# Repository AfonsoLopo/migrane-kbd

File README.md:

## MIGRANE

# Table of Contents: 
- [Specs](#Specs)
- [Assembly](#Assemby)
- [Firmware](#Firmware)

## Specs
<b>MCU</b> : STM32F446RCT6
<b>Number of Keys:</b> 64 Kailh choc hotswap sockets
<b>Number of LEDS:</b> 64 SK6812-mini e (1 per key) 
<b>Displays:</b> Adafruit 1.8" TFT Display
<b>Connection between halfs :</b> Serial over USB-C to USB-C cable
<b>Wire Debugger:</b> optional headers

## Assembly

    (TBD)

## Firmware

Board prepared to be used with qmk firmware.

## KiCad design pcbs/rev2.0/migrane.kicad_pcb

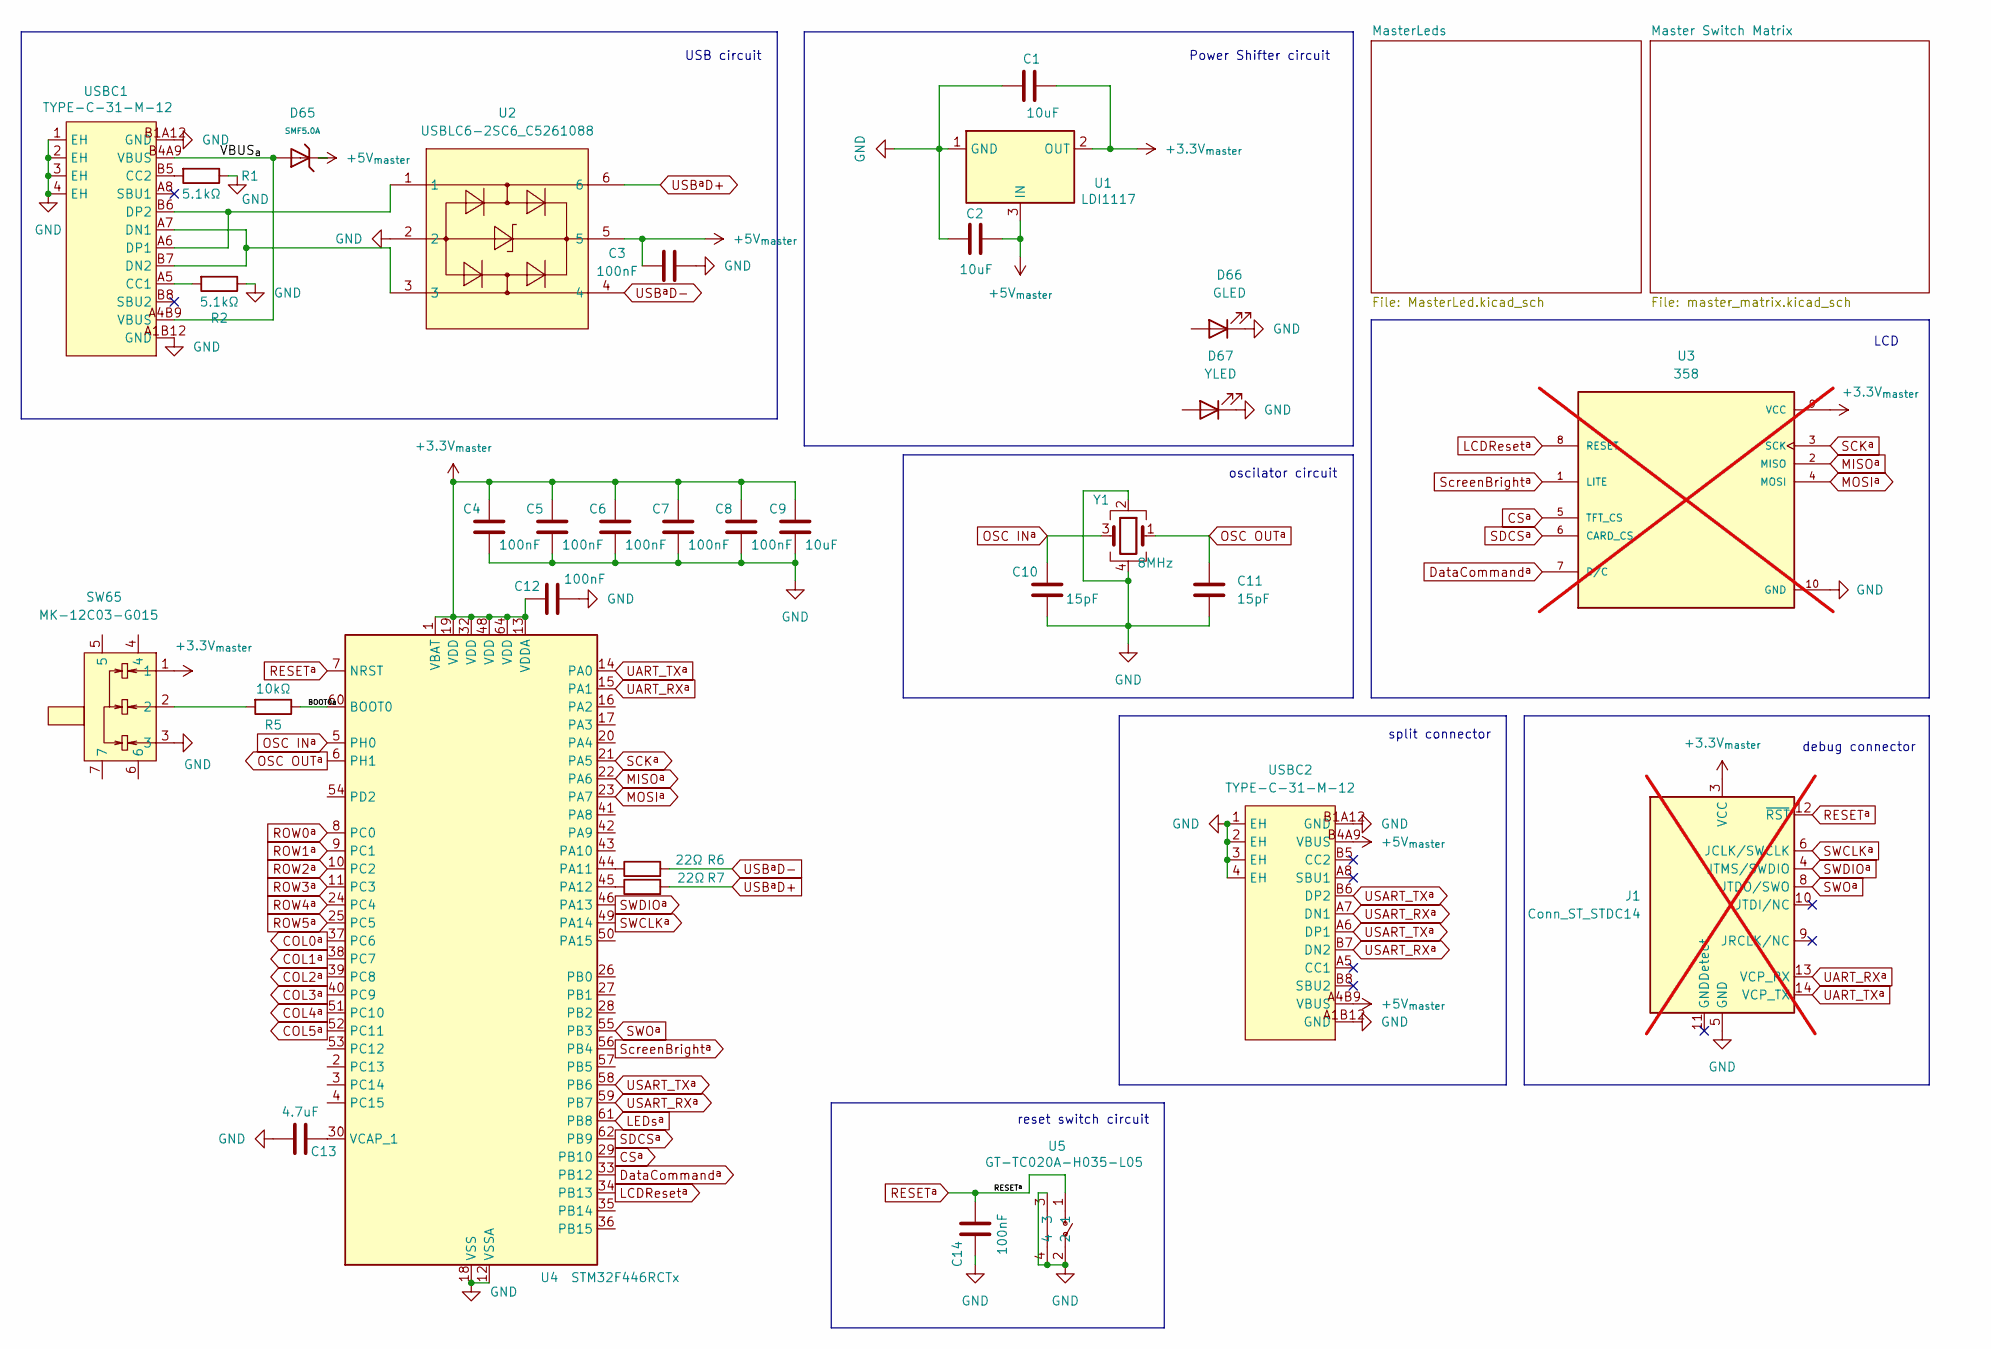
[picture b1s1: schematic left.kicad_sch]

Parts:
C1, C2, C9: 10uF; C_1206_3216Metric; LCSC C13585
C3, C4, C5, C6, C7, C8, C12, C14: 100nF; C_0805_2012Metric; LCSC C48579599
C10, C11: 15pF; C_0402_1005Metric; LCSC C441742
C13: 4.7uF; C_0603_1608Metric; LCSC C1705
D65: SMF5.0A; D_SOD-123FL; Part SMF5.0A; LCSC C19077497
D66: GLED; LED0805-R-RD; LCSC C84260
D67: YLED; LED0805-R-RD; LCSC C84261
J1: Conn_ST_STDC14; PinHeader_2x07_P1.27mm_Horizontal; not fitted
R1, R2: 5.1kΩ; R_0603_1608Metric; LCSC C2907114
R5: 10kΩ; R_0805_2012Metric; LCSC C84376
R6, R7: 22Ω; R_0402_1005Metric; LCSC C2906914
SW65: MK-12C03-G015; SW-SMD_MK-12C03-G015; LCSC Part C2890358
U1: LDI1117; SOT-223-3_TabPin2; LCSC C6186
U2: USBLC6-2SC6_C5261088; SOT-23-6_L2.9-W1.6-P0.95-LS2.8-BR; LCSC Part C5261088
U3: 358; MODULE_358; PARTREV 2021-12-09; not fitted
U4: STM32F446RCTx; LQFP-64_10x10mm_P0.5mm; LCSC C915971
U5: GT-TC020A-H035-L05; SW-SMD_GT-TC020B-H035-L05; LCSC Part C17179533
USBC1, USBC2: TYPE-C-31-M-12; USB-C_SMD-TYPE-C-31-M-12_1; LCSC Part C165948
Y1: 8MHz; Crystal_SMD_Abracon_ABM3B-4Pin_5.0x3.2mm; LCSC C1985378

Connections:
+3.3V_{master}: C1.1, C4.1, C5.1, C6.1, C7.1, C8.1, C9.1, C12.1, J1.3 (VCC), SW65.1, U1.2 (OUT), U3.9 (VCC), U4.1 (VBAT), U4.13 (VDDA), U4.19 (VDD), U4.32 (VDD), U4.48 (VDD), U4.64 (VDD); also elsewhere on the board
+5V_{master}: C2.2, C3.1, D65.1, U1.3 (IN), U2.5, USBC2.A4B9 (VBUS), USBC2.B4A9 (VBUS); also elsewhere on the board
/left/BOOT0a: R5.1, U4.60 (BOOT0)
/left/VBUS_{a}: D65.2, USBC1.A4B9 (VBUS), USBC1.B4A9 (VBUS)
COL0^{a}: U4.37 (PC6); also elsewhere on the board
COL1^{a}: U4.38 (PC7); also elsewhere on the board
COL2^{a}: U4.39 (PC8); also elsewhere on the board
COL3^{a}: U4.40 (PC9); also elsewhere on the board
COL4^{a}: U4.51 (PC10); also elsewhere on the board
COL5^{a}: U4.52 (PC11); also elsewhere on the board
CS^{a}: U3.5 (TFT_CS), U4.29 (PB10); also elsewhere on the board
DataCommand^{a}: U3.7 (D/C), U4.33 (PB12); also elsewhere on the board
GND: C1.2, C2.1, C3.2, C4.2, C5.2, C6.2, C7.2, C8.2, C9.2, C10.2, C11.2, C12.2, C13.1, C14.1, D66.1 (K), D67.1 (K), J1.5 (GND), J1.7 (GND), R1.1, R2.1, SW65.3, U1.1 (GND), U2.2, U3.10 (GND), U4.12 (VSSA), U4.18 (VSS), U4.31 (VSS), U4.47 (VSS), U4.63 (VSS), U5.2, U5.3, U5.4, USBC1.1 (EH), USBC1.2 (EH), USBC1.3 (EH), USBC1.4 (EH), USBC1.A1B12 (GND), USBC1.B1A12 (GND), USBC2.1 (EH), USBC2.2 (EH), USBC2.3 (EH), USBC2.4 (EH), USBC2.A1B12 (GND), USBC2.B1A12 (GND), Y1.2, Y1.4; also elsewhere on the board
LCDReset^{a}: U3.8 (RESET), U4.34 (PB13); also elsewhere on the board
LEDs^{a}: U4.61 (PB8); also elsewhere on the board
MISO^{a}: U3.2 (MISO), U4.22 (PA6); also elsewhere on the board
MOSI^{a}: U3.4 (MOSI), U4.23 (PA7); also elsewhere on the board
unnamed: R5.2, SW65.2
unnamed 175: R6.1, U4.44 (PA11); also elsewhere on the board
unnamed 176: R7.1, U4.45 (PA12); also elsewhere on the board
unnamed: C13.2, U4.30 (VCAP_1)
unnamed: R2.2, USBC1.A5 (CC1)
unnamed: R1.2, USBC1.B5 (CC2)
unnamed: U2.3, USBC1.A7 (DN1), USBC1.B7 (DN2)
unnamed: U2.1, USBC1.A6 (DP1), USBC1.B6 (DP2)
OSC IN^{a}: C10.1, U4.5 (PH0), Y1.3
OSC OUT^{a}: C11.1, U4.6 (PH1), Y1.1
RESET^{a}: C14.2, J1.12 (~RST), U4.7 (NRST), U5.1; also elsewhere on the board
ROW0^{a}: U4.8 (PC0); also elsewhere on the board
ROW1^{a}: U4.9 (PC1); also elsewhere on the board
ROW2^{a}: U4.10 (PC2); also elsewhere on the board
ROW3^{a}: U4.11 (PC3); also elsewhere on the board
ROW4^{a}: U4.24 (PC4); also elsewhere on the board
ROW5^{a}: U4.25 (PC5); also elsewhere on the board
SCK^{a}: U3.3 (SCK), U4.21 (PA5); also elsewhere on the board
SDCS^{a}: U3.6 (CARD_CS), U4.62 (PB9); also elsewhere on the board
SWCLK^{a}: J1.6 (JCLK/SWCLK), U4.49 (PA14); also elsewhere on the board
SWDIO^{a}: J1.4 (JTMS/SWDIO), U4.46 (PA13); also elsewhere on the board
SWO^{a}: J1.8 (JTDO/SWO), U4.55 (PB3); also elsewhere on the board
ScreenBright^{a}: U3.1 (LITE), U4.56 (PB4); also elsewhere on the board
UART_RX^{a}: J1.13 (VCP_RX), U4.15 (PA1); also elsewhere on the board
UART_TX^{a}: J1.14 (VCP_TX), U4.14 (PA0); also elsewhere on the board
USART_RX^{a}: U4.59 (PB7), USBC2.A7 (DN1), USBC2.B7 (DN2)
USART_TX^{a}: U4.58 (PB6), USBC2.A6 (DP1), USBC2.B6 (DP2)
USB^{a}D+: R7.2, U2.6
USB^{a}D-: R6.2, U2.4

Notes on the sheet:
split connector
oscilator circuit
reset switch circuit
debug connector
USB circuit
Power Shifter circuit
LCD

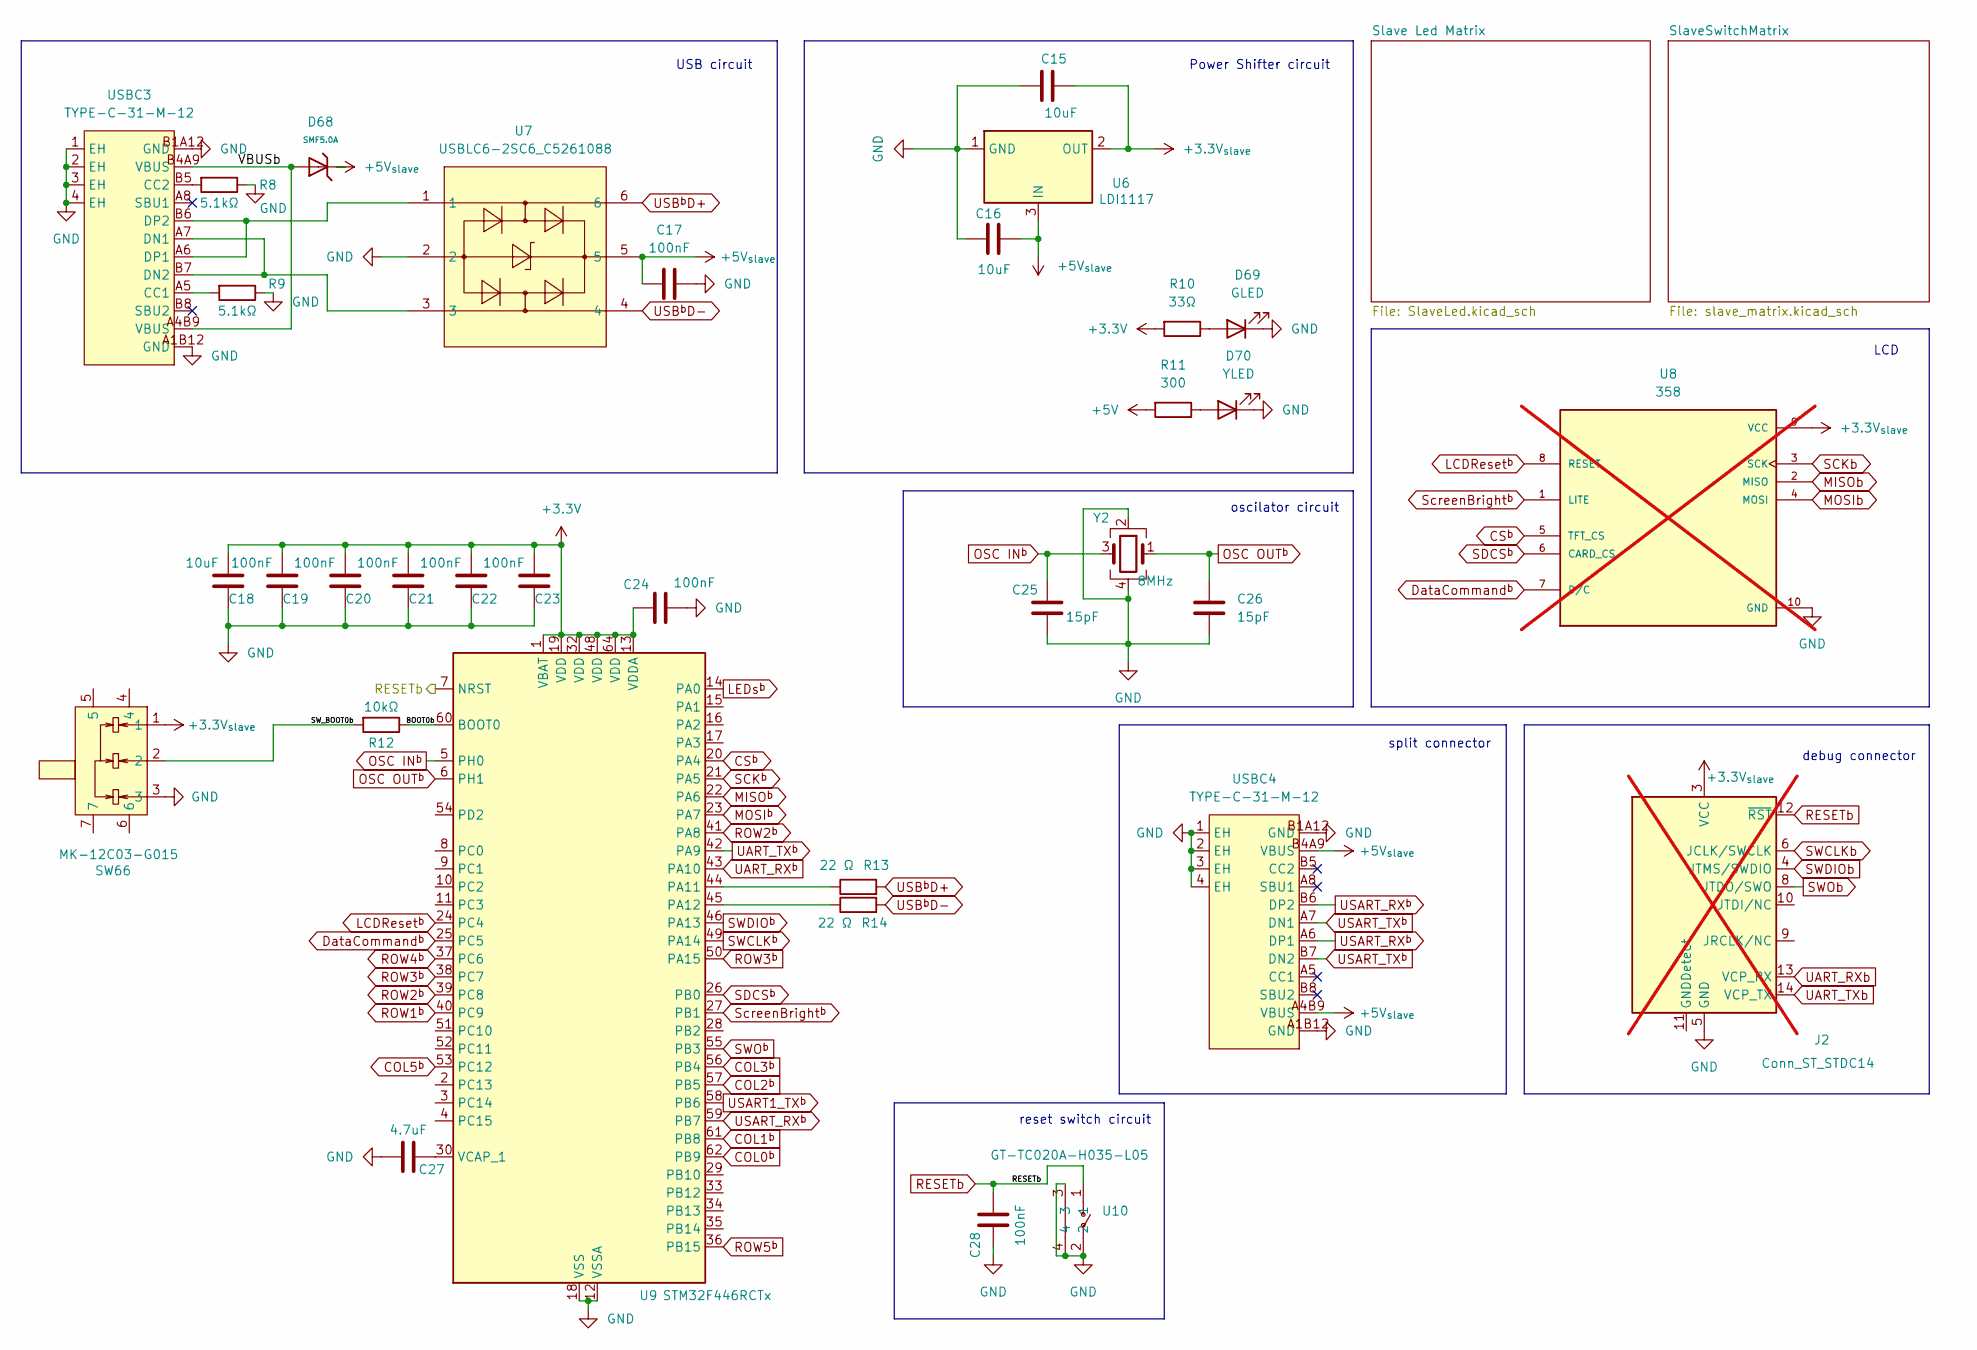
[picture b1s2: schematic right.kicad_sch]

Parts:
C15, C16, C18: 10uF; C_1206_3216Metric; LCSC C13585
C17, C19, C20, C21, C22, C23, C24, C28: 100nF; C_0805_2012Metric; LCSC C48579599
C25, C26: 15pF; C_0402_1005Metric; LCSC C441742
C27: 4.7uF; C_0603_1608Metric; LCSC C1705
D68: SMF5.0A; D_SOD-123FL; Part SMF5.0A; LCSC C19077497
D69: GLED; LED0805-R-RD; LCSC C84260
D70: YLED; LED0805-R-RD; LCSC C84261
J2: Conn_ST_STDC14; PinHeader_2x07_P1.27mm_Horizontal; not fitted
R8, R9: 5.1kΩ; R_0603_1608Metric; LCSC C2907114
R10: 33Ω; R_0603_1608Metric; LCSC C108661
R11: 300; R_0603_1608Metric; LCSC C2907148
R12: 10kΩ; R_0805_2012Metric; LCSC C84376
R13, R14: 22 Ω; R_0402_1005Metric; LCSC C2906914
SW66: MK-12C03-G015; SW-SMD_MK-12C03-G015; LCSC Part C2890358
U6: LDI1117; SOT-223-3_TabPin2; LCSC C6186
U7: USBLC6-2SC6_C5261088; SOT-23-6_L2.9-W1.6-P0.95-LS2.8-BR; LCSC Part C5261088
U8: 358; MODULE_358; PARTREV 2021-12-09; not fitted
U9: STM32F446RCTx; LQFP-64_10x10mm_P0.5mm; LCSC C915971
U10: GT-TC020A-H035-L05; SW-SMD_GT-TC020B-H035-L05; LCSC Part C17179533
USBC3, USBC4: TYPE-C-31-M-12; USB-C_SMD-TYPE-C-31-M-12_1; LCSC Part C165948
Y2: 8MHz; Crystal_SMD_Abracon_ABM3B-4Pin_5.0x3.2mm; LCSC C1985378

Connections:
+3.3V: C18.2, C19.2, C20.2, C21.2, C22.2, C23.2, C24.2, R10.2, U9.1 (VBAT), U9.13 (VDDA), U9.19 (VDD), U9.32 (VDD), U9.48 (VDD), U9.64 (VDD); also elsewhere on the board
+3.3V_{slave}: C15.1, J2.3 (VCC), SW66.1, U6.2 (OUT), U8.9 (VCC); also elsewhere on the board
+5V: R11.2; also elsewhere on the board
+5V_{slave}: C16.2, C17.1, D68.1, U6.3 (IN), U7.5, USBC4.A4B9 (VBUS), USBC4.B4A9 (VBUS); also elsewhere on the board
/right/BOOT0b: R12.1, U9.60 (BOOT0)
/right/SW_BOOT0b: R12.2, SW66.2; also elsewhere on the board
/right/VBUSb: D68.2, USBC3.A4B9 (VBUS), USBC3.B4A9 (VBUS)
COL0^{b}: U9.62 (PB9)
COL1^{b}: U9.61 (PB8)
COL2^{b}: U9.57 (PB5)
COL3^{b}: U9.56 (PB4)
COL5^{b}: U9.53 (PC12)
CS^{b}: U8.5 (TFT_CS), U9.20 (PA4)
DataCommand^{b}: U8.7 (D/C), U9.25 (PC5)
GND: C15.2, C16.1, C17.2, C18.1, C19.1, C20.1, C21.1, C22.1, C23.1, C24.1, C25.2, C26.2, C27.1, C28.1, D69.1 (K), D70.1 (K), J2.5 (GND), J2.7 (GND), R8.1, R9.1, SW66.3, U6.1 (GND), U7.2, U8.10 (GND), U9.12 (VSSA), U9.18 (VSS), U9.31 (VSS), U9.47 (VSS), U9.63 (VSS), U10.2, U10.3, U10.4, USBC3.1 (EH), USBC3.2 (EH), USBC3.3 (EH), USBC3.4 (EH), USBC3.A1B12 (GND), USBC3.B1A12 (GND), USBC4.1 (EH), USBC4.2 (EH), USBC4.3 (EH), USBC4.4 (EH), USBC4.A1B12 (GND), USBC4.B1A12 (GND), Y2.2, Y2.4; also elsewhere on the board
LCDReset^{b}: U8.8 (RESET), U9.24 (PC4)
LEDs^{b}: U9.14 (PA0)
MISO^{b}: U9.22 (PA6)
MISOb: U8.2 (MISO)
MOSI^{b}: U9.23 (PA7)
MOSIb: U8.4 (MOSI)
unnamed: D69.2 (A), R10.1
unnamed: D70.2 (A), R11.1
unnamed: R13.1, U9.44 (PA11)
unnamed: R14.1, U9.45 (PA12)
unnamed: C27.2, U9.30 (VCAP_1)
unnamed: R9.2, USBC3.A5 (CC1)
unnamed: R8.2, USBC3.B5 (CC2)
unnamed: U7.3, USBC3.A7 (DN1), USBC3.B7 (DN2)
unnamed: U7.1, USBC3.A6 (DP1), USBC3.B6 (DP2)
OSC IN^{b}: C25.1, U9.5 (PH0), Y2.3
OSC OUT^{b}: C26.1, U9.6 (PH1), Y2.1
RESETb: C28.2, J2.12 (~RST), U9.7 (NRST), U10.1; also elsewhere on the board
ROW1^{b}: U9.40 (PC9)
ROW2^{b}: U9.39 (PC8), U9.41 (PA8)
ROW3^{b}: U9.38 (PC7), U9.50 (PA15)
ROW4^{b}: U9.37 (PC6)
ROW5^{b}: U9.36 (PB15)
SCK^{b}: U9.21 (PA5)
SCKb: U8.3 (SCK)
SDCS^{b}: U8.6 (CARD_CS), U9.26 (PB0)
SWCLK^{b}: U9.49 (PA14)
SWCLKb: J2.6 (JCLK/SWCLK)
SWDIO^{b}: U9.46 (PA13)
SWDIOb: J2.4 (JTMS/SWDIO)
SWO^{b}: U9.55 (PB3)
SWOb: J2.8 (JTDO/SWO)
ScreenBright^{b}: U8.1 (LITE), U9.27 (PB1)
UART_RX^{b}: U9.43 (PA10)
UART_RXb: J2.13 (VCP_RX)
UART_TX^{b}: U9.42 (PA9)
UART_TXb: J2.14 (VCP_TX)
USART1_TX^{b}: U9.58 (PB6)
USART_RX^{b}: U9.59 (PB7), USBC4.A6 (DP1), USBC4.B6 (DP2)
USART_TX^{b}: USBC4.A7 (DN1), USBC4.B7 (DN2)
USB^{b}D+: R13.2, U7.6
USB^{b}D-: R14.2, U7.4

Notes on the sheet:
reset switch circuit
split connector
debug connector
Power Shifter circuit
oscilator circuit
USB circuit
LCD

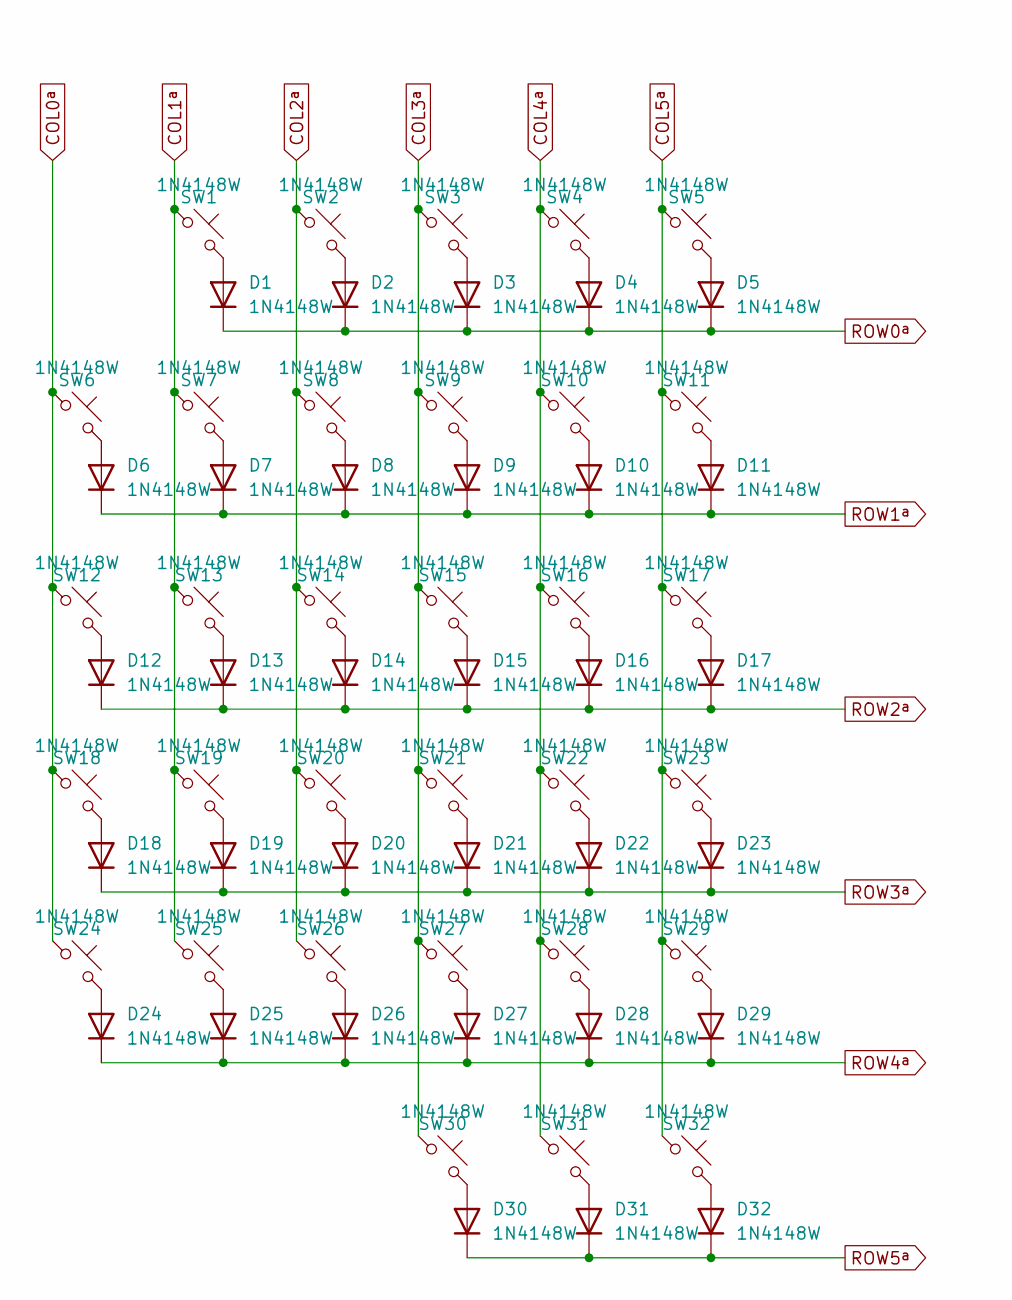
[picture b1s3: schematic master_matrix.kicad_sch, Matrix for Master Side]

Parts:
D1, D2, D3, D4, D5, D6, D7, D8, D9, D10, D11, D12, D13, D14, D15, D16, D17, D18, D19, D20, D21, D22, D23, D24, D25, D26, D27, D28, D29, D30, D31, D32: 1N4148W; D_SOD-123; LCSC C917030
SW1, SW2, SW3, SW4, SW5, SW6, SW7, SW8, SW9, SW10, SW11, SW12, SW13, SW14, SW15, SW16, SW17, SW18, SW19, SW20, SW21, SW22, SW23, SW24, SW25, SW26, SW27, SW28, SW29, SW30, SW31: 1N4148W; SW_Hotswap_Kailh_Choc_V1_Plated_1.00u; LCSC C917030
SW32: 1N4148W; SW_Hotswap_Kailh_Choc_V1_Plated_1.50u; LCSC C917030

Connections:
COL0^{a}: SW6.1, SW12.1, SW18.1, SW24.1; also elsewhere on the board
COL1^{a}: SW1.1, SW7.1, SW13.1, SW19.1, SW25.1; also elsewhere on the board
COL2^{a}: SW2.1, SW8.1, SW14.1, SW20.1, SW26.1; also elsewhere on the board
COL3^{a}: SW3.1, SW9.1, SW15.1, SW21.1, SW27.1, SW30.1; also elsewhere on the board
COL4^{a}: SW4.1, SW10.1, SW16.1, SW22.1, SW28.1, SW31.1; also elsewhere on the board
COL5^{a}: SW5.1, SW11.1, SW17.1, SW23.1, SW29.1, SW32.1; also elsewhere on the board
unnamed 44: D1.2 (A), SW1.2; also elsewhere on the board
unnamed: D2.2 (A), SW2.2
unnamed 46: D3.2 (A), SW3.2; also elsewhere on the board
unnamed 47: D4.2 (A), SW4.2; also elsewhere on the board
unnamed 48: D5.2 (A), SW5.2; also elsewhere on the board
unnamed 49: D6.2 (A), SW6.2; also elsewhere on the board
unnamed 50: D7.2 (A), SW7.2; also elsewhere on the board
unnamed 51: D8.2 (A), SW8.2; also elsewhere on the board
unnamed 52: D9.2 (A), SW9.2; also elsewhere on the board
unnamed 53: D10.2 (A), SW10.2; also elsewhere on the board
unnamed: D11.2 (A), SW11.2
unnamed 55: D12.2 (A), SW12.2; also elsewhere on the board
unnamed 56: D13.2 (A), SW13.2; also elsewhere on the board
unnamed 57: D14.2 (A), SW14.2; also elsewhere on the board
unnamed 58: D15.2 (A), SW15.2; also elsewhere on the board
unnamed 59: D16.2 (A), SW16.2; also elsewhere on the board
unnamed: D17.2 (A), SW17.2
unnamed: D18.2 (A), SW18.2
unnamed: D19.2 (A), SW19.2
unnamed: D20.2 (A), SW20.2
unnamed: D21.2 (A), SW21.2
unnamed: D22.2 (A), SW22.2
unnamed: D23.2 (A), SW23.2
unnamed: D24.2 (A), SW24.2
unnamed: D25.2 (A), SW25.2
unnamed: D26.2 (A), SW26.2
unnamed: D27.2 (A), SW27.2
unnamed: D28.2 (A), SW28.2
unnamed: D29.2 (A), SW29.2
unnamed: D30.2 (A), SW30.2
unnamed: D31.2 (A), SW31.2
unnamed: D32.2 (A), SW32.2
ROW0^{a}: D1.1 (K), D2.1 (K), D3.1 (K), D4.1 (K), D5.1 (K); also elsewhere on the board
ROW1^{a}: D6.1 (K), D7.1 (K), D8.1 (K), D9.1 (K), D10.1 (K), D11.1 (K); also elsewhere on the board
ROW2^{a}: D12.1 (K), D13.1 (K), D14.1 (K), D15.1 (K), D16.1 (K), D17.1 (K); also elsewhere on the board
ROW3^{a}: D18.1 (K), D19.1 (K), D20.1 (K), D21.1 (K), D22.1 (K), D23.1 (K); also elsewhere on the board
ROW4^{a}: D24.1 (K), D25.1 (K), D26.1 (K), D27.1 (K), D28.1 (K), D29.1 (K); also elsewhere on the board
ROW5^{a}: D30.1 (K), D31.1 (K), D32.1 (K); also elsewhere on the board

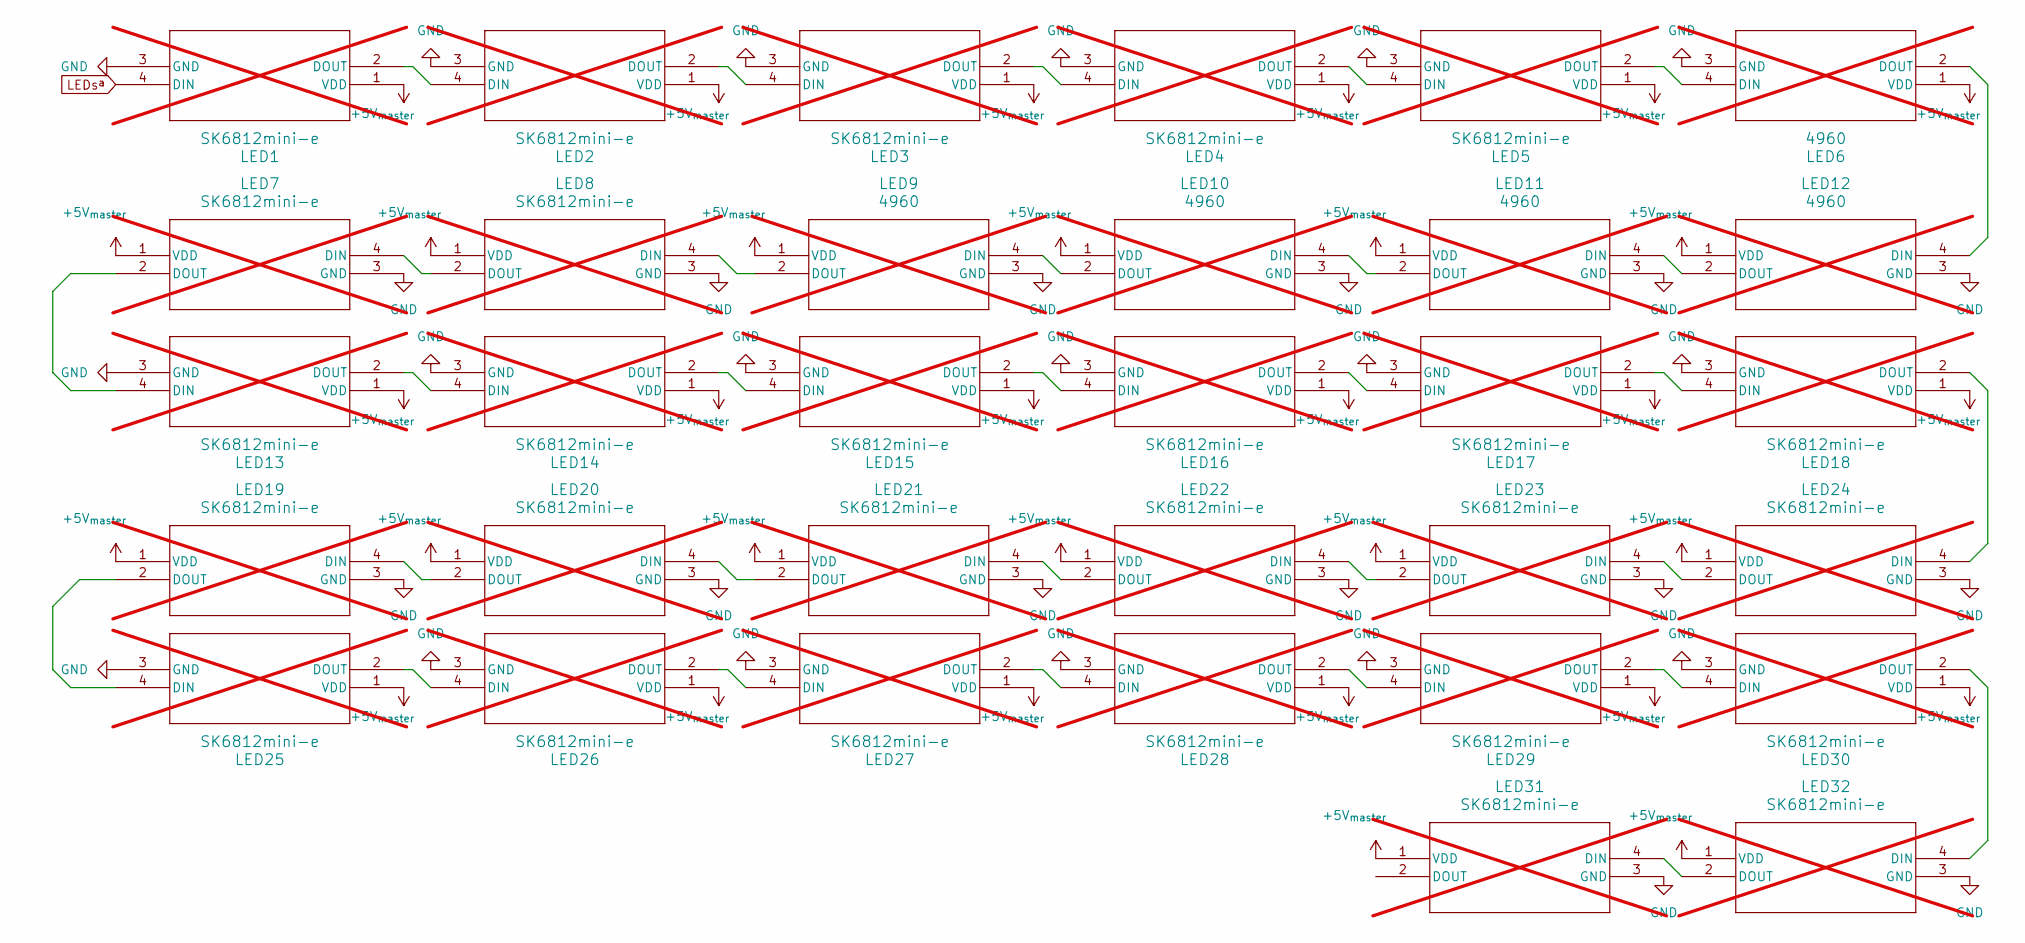
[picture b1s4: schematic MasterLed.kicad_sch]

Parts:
LED1, LED2, LED3, LED4, LED5, LED7, LED8, LED13, LED14, LED15, LED16, LED17, LED18, LED19, LED20, LED21, LED22, LED23, LED24, LED25, LED26, LED27, LED28, LED29, LED30, LED31, LED32: SK6812mini-e; LED-SMD_L3.2-W2.8-LS5.9_SK6812MINI-E; not fitted
LED6, LED9, LED10, LED11, LED12: 4960; LED-SMD_L3.2-W2.8-LS5.9_SK6812MINI-E; not fitted

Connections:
+5V_{master}: LED1.1 (VDD), LED2.1 (VDD), LED3.1 (VDD), LED4.1 (VDD), LED5.1 (VDD), LED6.1 (VDD), LED7.1 (VDD), LED8.1 (VDD), LED9.1 (VDD), LED10.1 (VDD), LED11.1 (VDD), LED12.1 (VDD), LED13.1 (VDD), LED14.1 (VDD), LED15.1 (VDD), LED16.1 (VDD), LED17.1 (VDD), LED18.1 (VDD), LED19.1 (VDD), LED20.1 (VDD), LED21.1 (VDD), LED22.1 (VDD), LED23.1 (VDD), LED24.1 (VDD), LED25.1 (VDD), LED26.1 (VDD), LED27.1 (VDD), LED28.1 (VDD), LED29.1 (VDD), LED30.1 (VDD), LED31.1 (VDD), LED32.1 (VDD); also elsewhere on the board
GND: LED1.3 (GND), LED2.3 (GND), LED3.3 (GND), LED4.3 (GND), LED5.3 (GND), LED6.3 (GND), LED7.3 (GND), LED8.3 (GND), LED9.3 (GND), LED10.3 (GND), LED11.3 (GND), LED12.3 (GND), LED13.3 (GND), LED14.3 (GND), LED15.3 (GND), LED16.3 (GND), LED17.3 (GND), LED18.3 (GND), LED19.3 (GND), LED20.3 (GND), LED21.3 (GND), LED22.3 (GND), LED23.3 (GND), LED24.3 (GND), LED25.3 (GND), LED26.3 (GND), LED27.3 (GND), LED28.3 (GND), LED29.3 (GND), LED30.3 (GND), LED31.3 (GND), LED32.3 (GND); also elsewhere on the board
LEDs^{a}: LED1.4 (DIN); also elsewhere on the board
unnamed: LED1.2 (DOUT), LED2.4 (DIN)
unnamed: LED2.2 (DOUT), LED3.4 (DIN)
unnamed: LED3.2 (DOUT), LED4.4 (DIN)
unnamed: LED4.2 (DOUT), LED5.4 (DIN)
unnamed: LED5.2 (DOUT), LED6.4 (DIN)
unnamed 117: LED7.4 (DIN), LED8.2 (DOUT); also elsewhere on the board
unnamed: LED8.4 (DIN), LED9.2 (DOUT)
unnamed: LED10.4 (DIN), LED11.2 (DOUT)
unnamed: LED9.4 (DIN), LED10.2 (DOUT)
unnamed: LED11.4 (DIN), LED12.2 (DOUT)
unnamed: LED6.2 (DOUT), LED12.4 (DIN)
unnamed 123: LED7.2 (DOUT), LED13.4 (DIN); also elsewhere on the board
unnamed: LED13.2 (DOUT), LED14.4 (DIN)
unnamed: LED14.2 (DOUT), LED15.4 (DIN)
unnamed: LED15.2 (DOUT), LED16.4 (DIN)
unnamed: LED16.2 (DOUT), LED17.4 (DIN)
unnamed 128: LED17.2 (DOUT), LED18.4 (DIN); also elsewhere on the board
unnamed 129: LED18.2 (DOUT), LED24.4 (DIN); also elsewhere on the board
unnamed: LED19.4 (DIN), LED20.2 (DOUT)
unnamed: LED19.2 (DOUT), LED25.4 (DIN)
unnamed: LED20.4 (DIN), LED21.2 (DOUT)
unnamed: LED21.4 (DIN), LED22.2 (DOUT)
unnamed: LED22.4 (DIN), LED23.2 (DOUT)
unnamed 135: LED23.4 (DIN), LED24.2 (DOUT); also elsewhere on the board
unnamed: LED25.2 (DOUT), LED26.4 (DIN)
unnamed: LED26.2 (DOUT), LED27.4 (DIN)
unnamed: LED27.2 (DOUT), LED28.4 (DIN)
unnamed: LED28.2 (DOUT), LED29.4 (DIN)
unnamed: LED29.2 (DOUT), LED30.4 (DIN)
unnamed: LED30.2 (DOUT), LED32.4 (DIN)
unnamed: LED31.4 (DIN), LED32.2 (DOUT)

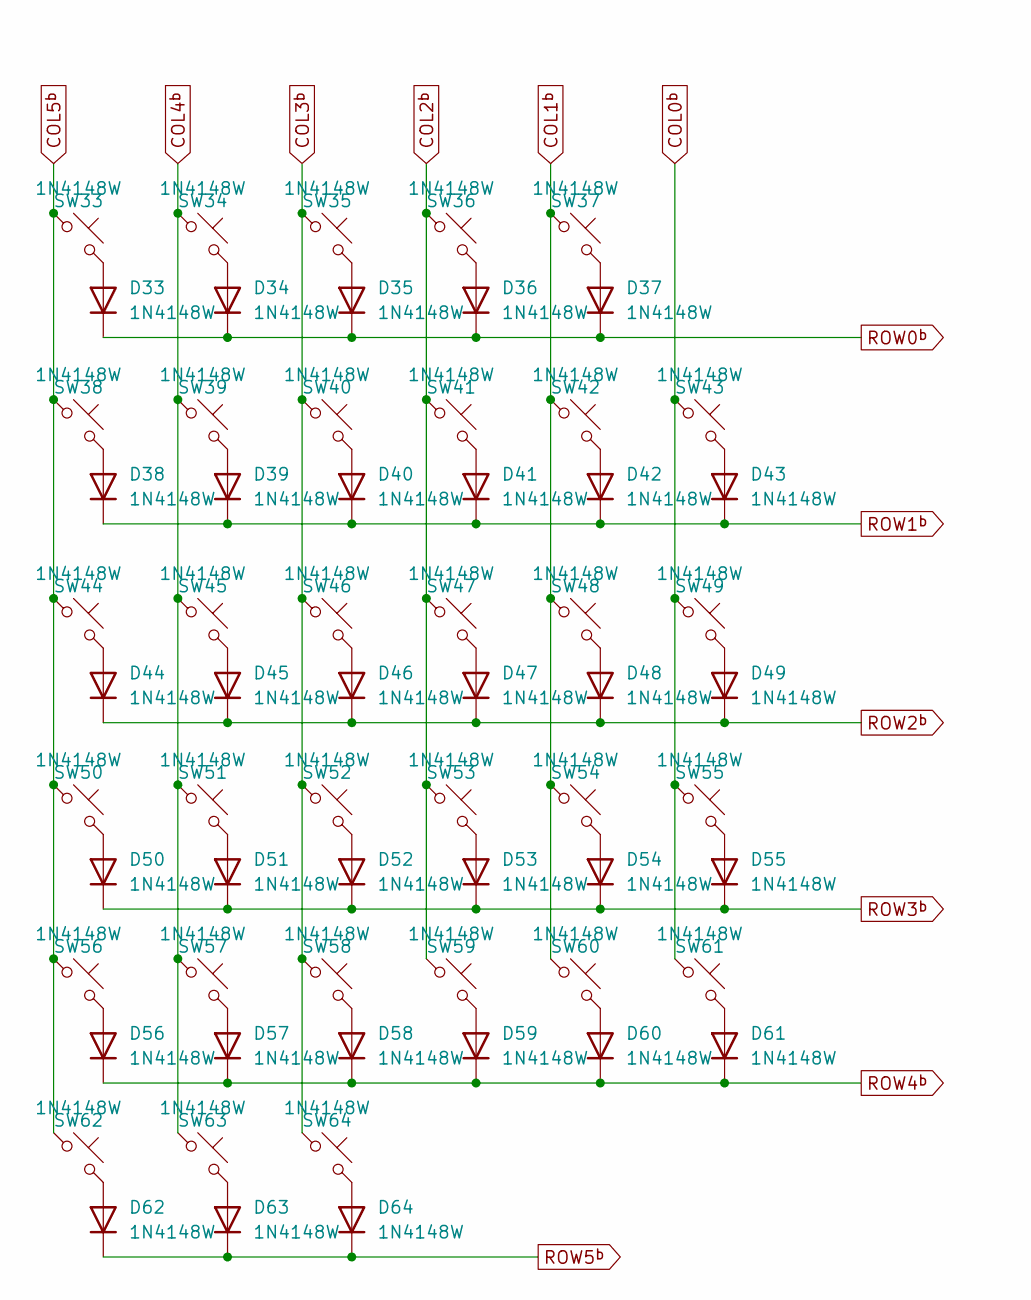
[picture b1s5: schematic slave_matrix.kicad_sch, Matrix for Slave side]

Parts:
D33, D34, D35, D36, D37, D38, D39, D40, D41, D42, D43, D44, D45, D46, D47, D48, D49, D50, D51, D52, D53, D54, D55, D56, D57, D58, D59, D60, D61, D62, D63, D64: 1N4148W; D_SOD-123; LCSC C917030
SW33, SW34, SW35, SW36, SW37, SW38, SW39, SW40, SW41, SW42, SW43, SW44, SW45, SW46, SW47, SW48, SW49, SW50, SW51, SW52, SW53, SW54, SW55, SW56, SW57, SW58, SW59, SW60, SW61, SW63, SW64: 1N4148W; SW_Hotswap_Kailh_Choc_V1_Plated_1.00u; LCSC C917030
SW62: 1N4148W; SW_Hotswap_Kailh_Choc_V1_Plated_1.50u; LCSC C917030

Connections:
COL0b: SW43.1, SW49.1, SW55.1, SW61.1
COL1b: SW37.1, SW42.1, SW48.1, SW54.1, SW60.1
COL2b: SW36.1, SW41.1, SW47.1, SW53.1, SW59.1
COL3b: SW35.1, SW40.1, SW46.1, SW52.1, SW58.1, SW64.1
COL4b: SW34.1, SW39.1, SW45.1, SW51.1, SW57.1, SW63.1
COL5b: SW33.1, SW38.1, SW44.1, SW50.1, SW56.1, SW62.1
unnamed: D33.2 (A), SW33.2
unnamed: D34.2 (A), SW34.2
unnamed: D35.2 (A), SW35.2
unnamed: D36.2 (A), SW36.2
unnamed: D37.2 (A), SW37.2
unnamed: D38.2 (A), SW38.2
unnamed: D39.2 (A), SW39.2
unnamed: D40.2 (A), SW40.2
unnamed: D41.2 (A), SW41.2
unnamed: D42.2 (A), SW42.2
unnamed: D43.2 (A), SW43.2
unnamed: D44.2 (A), SW44.2
unnamed: D45.2 (A), SW45.2
unnamed: D46.2 (A), SW46.2
unnamed: D47.2 (A), SW47.2
unnamed: D48.2 (A), SW48.2
unnamed: D49.2 (A), SW49.2
unnamed: D50.2 (A), SW50.2
unnamed: D51.2 (A), SW51.2
unnamed: D52.2 (A), SW52.2
unnamed: D53.2 (A), SW53.2
unnamed: D54.2 (A), SW54.2
unnamed: D55.2 (A), SW55.2
unnamed: D56.2 (A), SW56.2
unnamed: D57.2 (A), SW57.2
unnamed: D58.2 (A), SW58.2
unnamed: D59.2 (A), SW59.2
unnamed: D60.2 (A), SW60.2
unnamed: D61.2 (A), SW61.2
unnamed: D62.2 (A), SW62.2
unnamed: D63.2 (A), SW63.2
unnamed: D64.2 (A), SW64.2
ROW0b: D33.1 (K), D34.1 (K), D35.1 (K), D36.1 (K), D37.1 (K)
ROW1b: D38.1 (K), D39.1 (K), D40.1 (K), D41.1 (K), D42.1 (K), D43.1 (K)
ROW2b: D44.1 (K), D45.1 (K), D46.1 (K), D47.1 (K), D48.1 (K), D49.1 (K)
ROW3b: D50.1 (K), D51.1 (K), D52.1 (K), D53.1 (K), D54.1 (K), D55.1 (K)
ROW4b: D56.1 (K), D57.1 (K), D58.1 (K), D59.1 (K), D60.1 (K), D61.1 (K)
ROW5b: D62.1 (K), D63.1 (K), D64.1 (K)
